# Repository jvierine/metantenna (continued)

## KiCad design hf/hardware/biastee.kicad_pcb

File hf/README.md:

# Broadband HF active dipole — development prototype

Balanced high-impedance X/Y inputs use paired MMBFJ310 JFET followers and BC850C output buffers. The nominal passband is 0.1–30 MHz. Only the X coax carries 12 V DC; both polarizations have common-mode filtering at the indoor bias board.

**This prototype is not RF-qualified or ready to order.** Native CAD checks pass, but the complete antenna/noise target, stability, blocker linearity and installed common-mode suppression still require validation. High input resistance alone does not establish sensitivity.

## Antenna head

## Indoor bias tee

The bias tee sits beside the receiver; the amplifier sits at the antenna. Only X supplies DC, while both coax paths include common-mode filtering.

- [KiCad schematic and PCB sources](hardware/)
- [Circuit overview](frontend.pdf)
- [Simulation and noise screening](../simulation/hf/)
- [Input-stage screening](docs/hf_frontend_screening.png)
- [Common-mode choke screening](docs/hf_choke_screening.png)
- [Shared enclosure sources](../mechanical/)

Shared generators remain in [`../hardware/`](../hardware/): `build_hf.py`, `finalize_hf.py` and `check_hf_native.py`. Use base conda Python. The mechanical interfaces reuse the VHF connector positions; confirm the exact assembled parts against the case before manufacture.

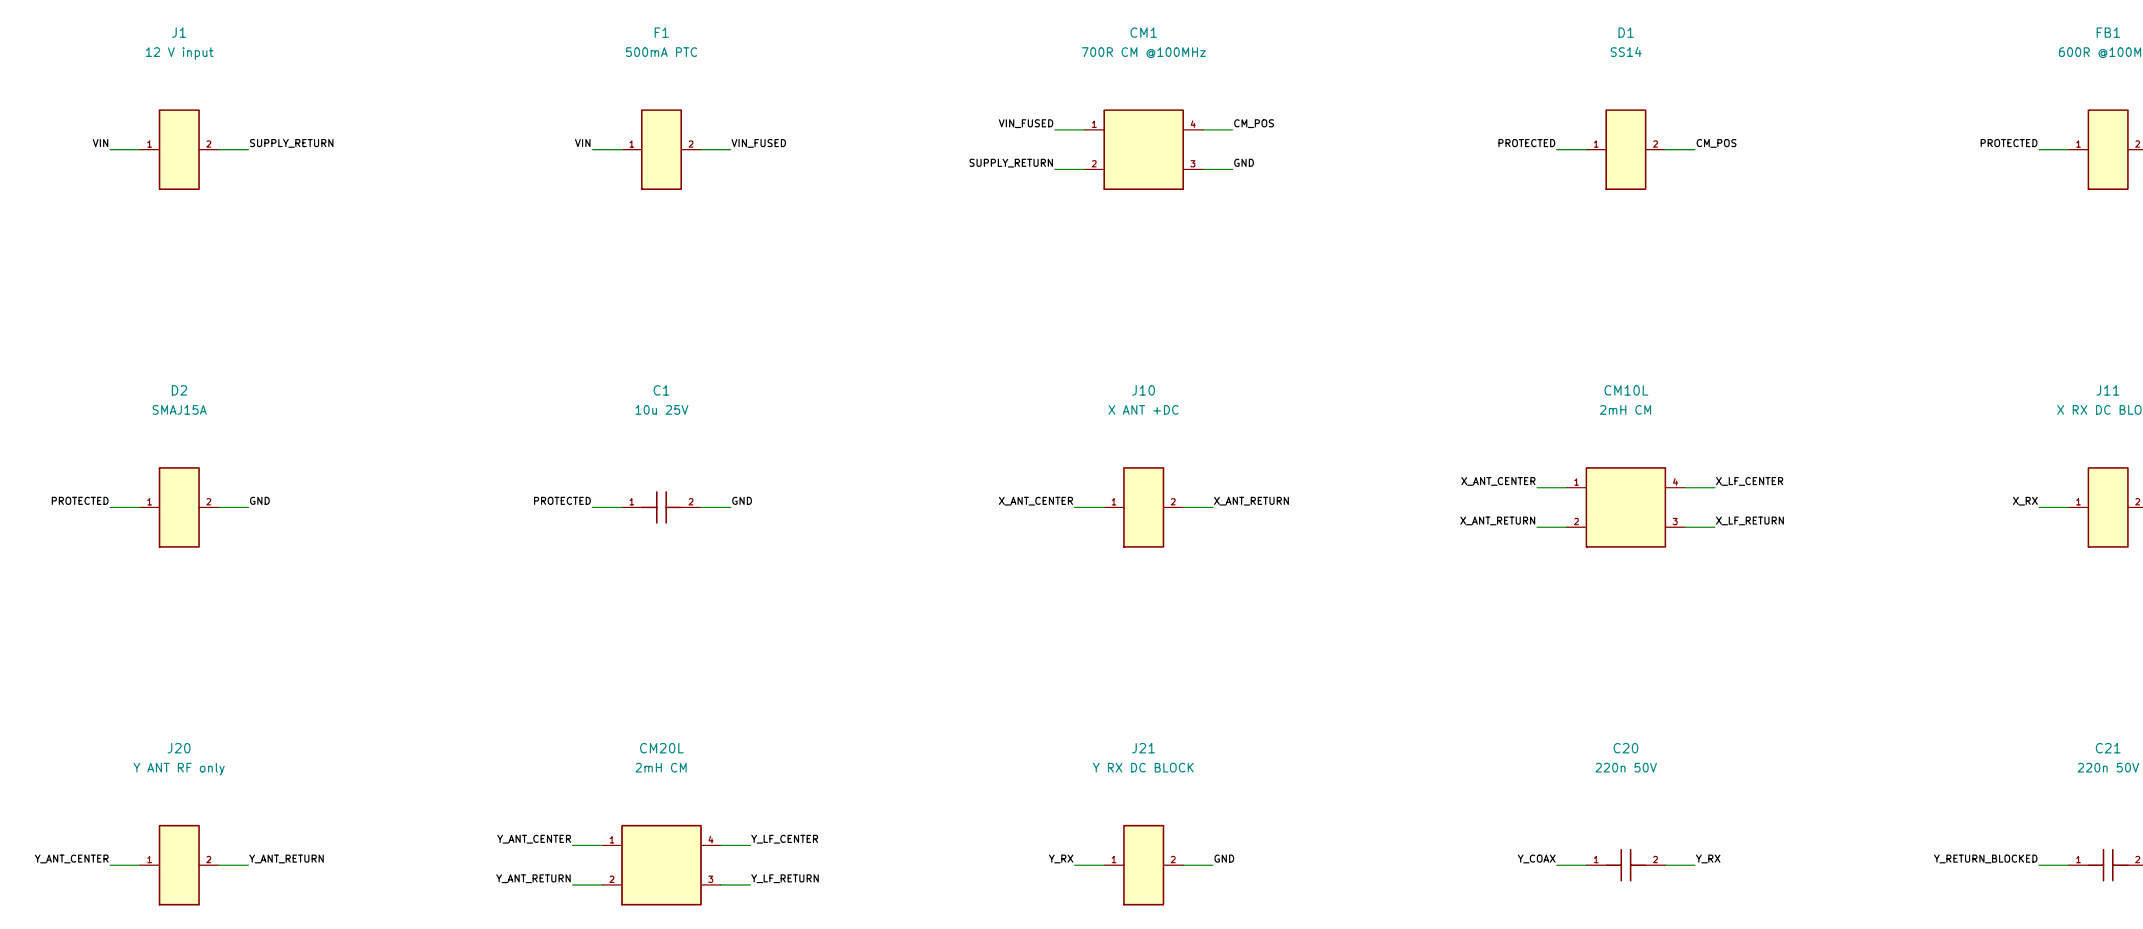
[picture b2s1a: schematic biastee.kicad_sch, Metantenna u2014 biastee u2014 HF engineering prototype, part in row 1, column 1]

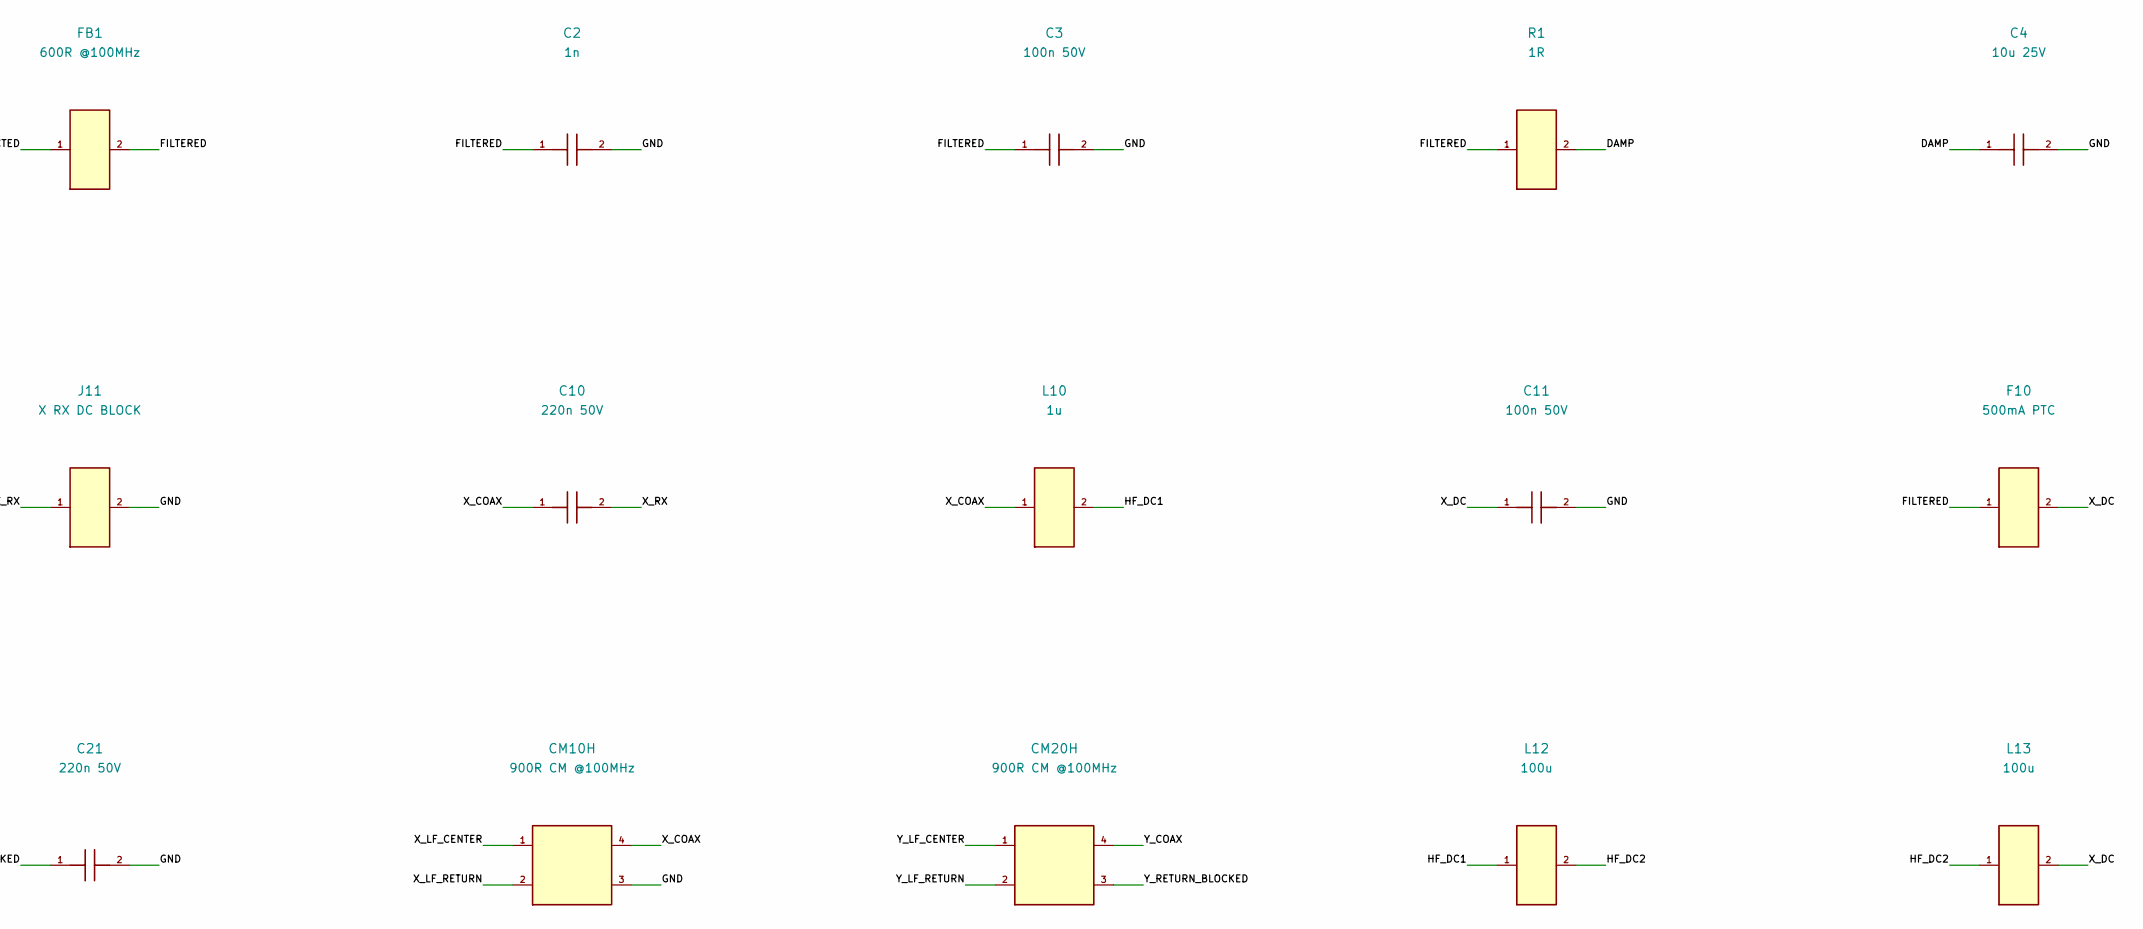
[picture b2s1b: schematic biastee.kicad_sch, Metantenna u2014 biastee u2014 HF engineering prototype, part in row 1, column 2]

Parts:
C1, C4: 10u 25V; 1206; MPN GRM31CR61E106KA12L
C2: 1n; 0805; MPN C0805C102J5GACTU
C3, C11: 100n 50V; 0805; MPN GRM21BR71H104KA01L
C10, C20, C21: 220n 50V; 0805; MPN GRM21BR71H224KA01L
CM1: 700R CM @100MHz; ACM7060; MPN ACM7060-701-2PL-TL01
CM10H, CM20H: 900R CM @100MHz; ACM4520; MPN ACM4520-901-2P-T000
CM10L, CM20L: 2mH CM; SRF0905; MPN SRF0905-202Y
D1: SS14; SMA_DIODE; MPN SS14
D2: SMAJ15A; SMA_DIODE; MPN SMAJ15A
F1, F10: 500mA PTC; 1206; MPN 1206L050/24YR
FB1: 600R @100MHz; 0805; MPN BLM21PG601SN1D
J1: 12 V input; TERM2; MPN 1729128
J10: X ANT +DC; SMA_RA; MPN SMA-KWE-323C-H13X23-LW
J11: X RX DC BLOCK; SMA_RA; MPN SMA-KWE-323C-H13X23-LW
J20: Y ANT RF only; SMA_RA; MPN SMA-KWE-323C-H13X23-LW
J21: Y RX DC BLOCK; SMA_RA; MPN SMA-KWE-323C-H13X23-LW
L10: 1u; 1008; MPN 1008CS-102XJRC
L12, L13: 100u; SRN6045; MPN SRN6045-101M
R1: 1R; 0805; MPN RC0805FR-071RL

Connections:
/CM_POS: CM1.4, D1.2
/DAMP: C4.1, R1.2
/FILTERED: C2.1, C3.1, F10.1, FB1.2, R1.1
/GND: C1.2, C2.2, C3.2, C4.2, C11.2, C21.2, CM1.3, CM10H.3, D2.2, J11.2, J21.2
/HF_DC1: L10.2, L12.1
/HF_DC2: L12.2, L13.1
/PROTECTED: C1.1, D1.1, D2.1, FB1.1
/SUPPLY_RETURN: CM1.2, J1.2
/VIN: F1.1, J1.1
/VIN_FUSED: CM1.1, F1.2
/X_ANT_CENTER: CM10L.1, J10.1
/X_ANT_RETURN: CM10L.2, J10.2
/X_COAX: C10.1, CM10H.4, L10.1
/X_DC: C11.1, F10.2, L13.2
/X_LF_CENTER: CM10H.1, CM10L.4
/X_LF_RETURN: CM10H.2, CM10L.3
/X_RX: C10.2, J11.1
/Y_ANT_CENTER: CM20L.1, J20.1
/Y_ANT_RETURN: CM20L.2, J20.2
/Y_COAX: C20.1, CM20H.4
/Y_LF_CENTER: CM20H.1, CM20L.4
/Y_LF_RETURN: CM20H.2, CM20L.3
/Y_RETURN_BLOCKED: C21.1, CM20H.3
/Y_RX: C20.2, J21.1

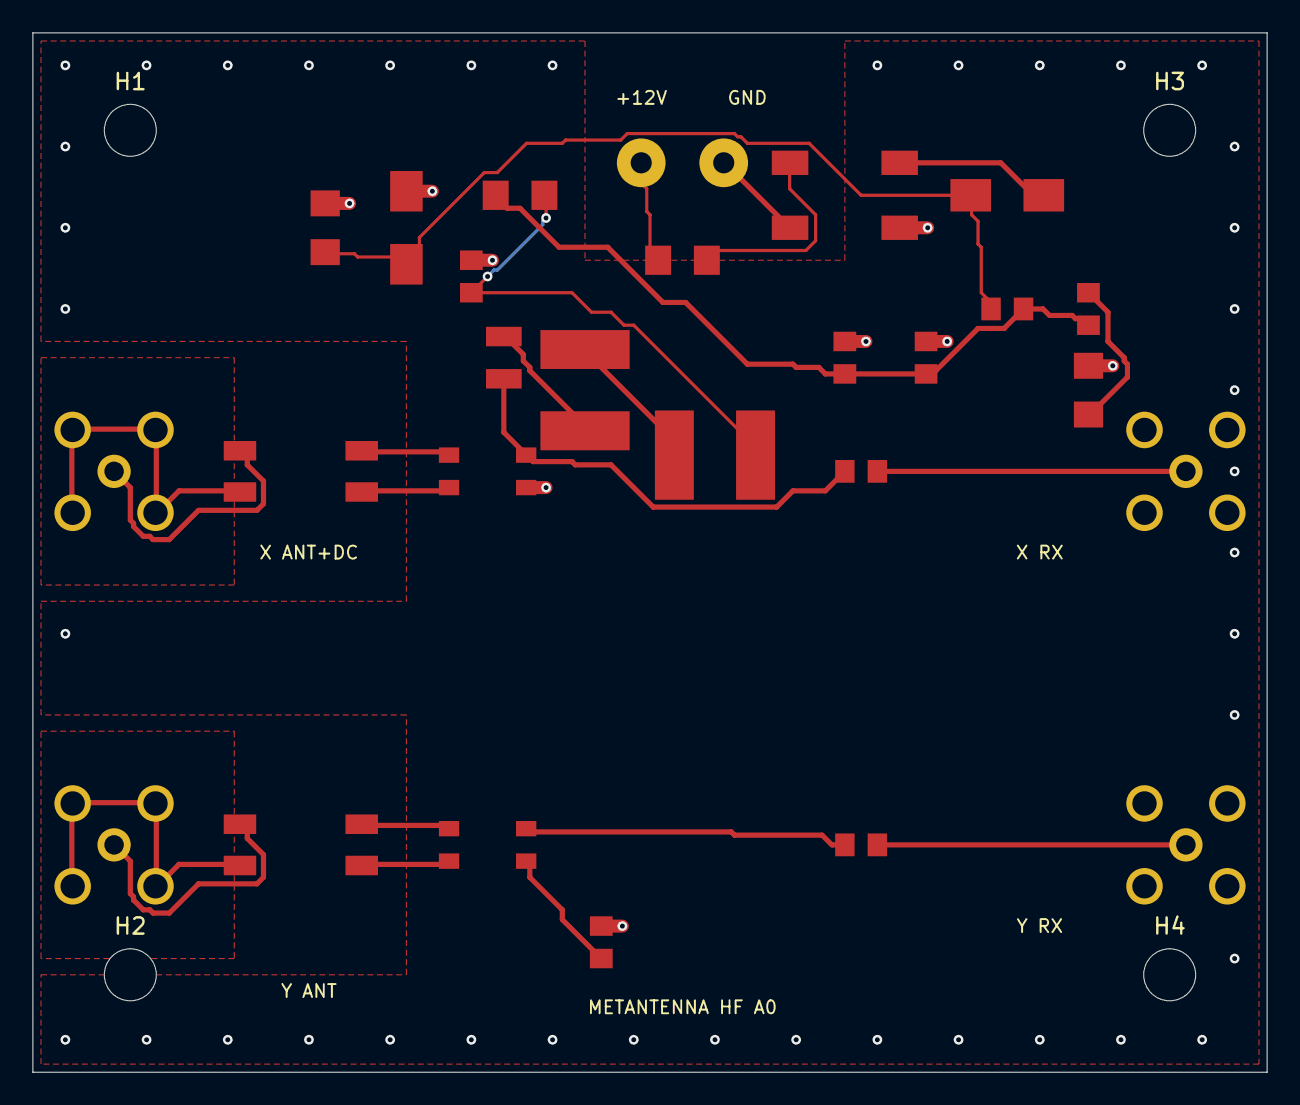
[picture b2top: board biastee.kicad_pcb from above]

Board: 4 copper layers, 76.0 x 64.0 mm, 31 parts (0 on the bottom side), 24 nets.

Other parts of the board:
H1, H2, H3, H4: MountingHole

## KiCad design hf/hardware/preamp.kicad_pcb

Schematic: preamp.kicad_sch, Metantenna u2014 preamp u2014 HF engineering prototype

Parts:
C108, C109, C130, C140, C208, C209, C230, C240: 220n 50V; 0805; MPN GRM21BR71H224KA01L
C110, C112, C210, C212: 10u 25V; 1206; MPN GRM31CR61E106KA12L
C111, C114, C211, C214: 100n 50V; 0805; MPN GRM21BR71H104KA01L
C113, C213: 10n 50V; 0805; MPN GRM21BR71H103KA01L
C131, C141, C231, C241: 100n; 0805; MPN GRM21BR71H104KA01L
C160, C161, C260, C261: 33n; 0805; MPN C0805C333J5GACTU
C162, C164, C262, C264: 130p; 0805; MPN C0805C131J5GACTU
C163, C263: 220p; 0805; MPN C0805C221J5GACTU
D103: SS14; SMA_DIODE; MPN SS14
D104: SMAJ15A; SMA_DIODE; MPN SMAJ15A
J101: X dipole; ANT_M3
J102: X RF +12V; SMA; MPN SMA-KE-347A-H13.5-P
J201: Y dipole; ANT_M3
J202: Y RF, DC blocked; SMA; MPN SMA-KE-347A-H13.5-P
L104: 1u; 1008; MPN 1008CS-102XJRC
L105, L106, L107, L205: 100u; SRN6045; MPN SRN6045-101M
L160, L260: 39u; 1008; MPN 1008CS-393XJLC
L161, L164, L261, L264: 120n; 0805; MPN 0805HP-121XGRC
L162, L163, L262, L263: 470n; 0805; MPN 0805HP-471XGRC
Q130, Q140, Q230, Q240: MMBFJ310LT1G; SOT23; MPN MMBFJ310LT1G
Q131, Q141, Q231, Q241: BC850C,235; SOT23; MPN BC850C,235
R103, R105, R203, R205: 294; 0805; MPN RC0805FR-07294RL
R104, R204: 18; 0805; MPN RC0805FR-0718RL
R106, R206: 40.2k; 0805; MPN RC0805FR-0740K2L
R107, R207: 10k; 0805; MPN RC0805FR-0710KL
R108, R208: 15 1W; 2512; MPN CRCW251215R0FKEG
R130, R140, R230, R240: 1M; 0805; MPN RC0805FR-071ML
R131, R141, R231, R241: 180; 0805; MPN RC0805FR-07180RL
R132, R142, R232, R242: 220; 0805; MPN RC0805FR-07220RL
R133, R143, R233, R243: 2.2; 0805; MPN RC0805FR-072R2L
R134, R144, R234, R244: 10; 0805; MPN RC0805FR-0710RL
R160, R260: 39; 0805; MPN RC0805FR-0739RL
T101, T201: ADT1-6T+; CD542; MPN ADT1-6T+
U101, U201: GALI-74+; SOT89; MPN GALI-74+
U102, U202: TPS7A4901DGNR; MSOP8EP; MPN TPS7A4901DGNR

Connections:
/GND: C110.2, C111.2, C112.2, C113.2, C114.2, C131.2, C141.2, C162.2, C163.2, C164.2, C210.2, C211.2, C212.2, C213.2, C214.2, C231.2, C241.2, C262.2, C263.2, C264.2, D104.2, J102.2, J202.2, L160.2, L260.2, R103.2, R105.2, R107.2, R130.2, R131.2, R132.2, R140.2, R141.2, R142.2, R203.2, R205.2, R207.2, R230.2, R231.2, R232.2, R240.2, R241.2, R242.2, T101.6, T201.6, U101.2 (GND), U102.4 (GND), U102.9 (EP), U201.2 (GND), U202.4 (GND), U202.9 (EP)
/HF_PWR1: L104.2, L106.1
/HF_PWR2: L106.2, L107.1
/V12: C110.1, C111.1, C210.1, C211.1, D103.1, D104.1, U102.5 (EN), U102.8 (IN), U202.5 (EN), U202.8 (IN)
/X_AC_N: C130.2, R133.1
/X_AC_P: C140.2, R143.1
/X_AMP_IN: L164.2, U101.1 (IN)
/X_AMP_OUT: C108.1, L105.2, U101.3 (OUT/DC)
/X_ANT_N: J101.1, Q130.3, R130.1
/X_ANT_P: J101.2, Q140.3, R140.1
/X_BAL_N: R133.2, T101.1
/X_BAL_P: R143.2, T101.3
/X_BIAS: L105.1, R108.2
/X_COAX: C109.2, J102.1, L104.1
/X_D_N: C131.1, Q130.1, R134.2
/X_D_P: C141.1, Q140.1, R144.2
/X_EF_N: C130.1, Q131.2, R132.1
/X_EF_P: C140.1, Q141.2, R142.1
/X_FB: R106.2, R107.1, U102.2 (FB)
/X_HP0: C160.1, R160.2
/X_HP1: C160.2, C161.1, L160.1
/X_LP0: C161.2, L161.1
/X_LP1: C162.1, L161.2, L162.1
/X_LP2: C163.1, L162.2, L163.1
/X_LP3: C164.1, L163.2, L164.1
/X_NR: C113.1, U102.6 (NR/SS)
/X_PAD_IN: C108.2, R103.1, R104.1
/X_PAD_OUT: C109.1, R104.2, R105.1
/X_RAW: D103.2, L107.2
/X_RF_IN: R160.1, T101.4
/X_SF_N: Q130.2, Q131.1, R131.1
/X_SF_P: Q140.2, Q141.1, R141.1
/X_V8: C112.1, C114.1, Q131.3, Q141.3, R106.1, R108.1, R134.1, R144.1, U102.1 (OUT)
/Y_AC_N: C230.2, R233.1
/Y_AC_P: C240.2, R243.1
/Y_AMP_IN: L264.2, U201.1 (IN)
/Y_AMP_OUT: C208.1, L205.2, U201.3 (OUT/DC)
/Y_ANT_N: J201.1, Q230.3, R230.1
/Y_ANT_P: J201.2, Q240.3, R240.1
/Y_BAL_N: R233.2, T201.1
/Y_BAL_P: R243.2, T201.3
/Y_BIAS: L205.1, R208.2
/Y_COAX: C209.2, J202.1
/Y_D_N: C231.1, Q230.1, R234.2
/Y_D_P: C241.1, Q240.1, R244.2
/Y_EF_N: C230.1, Q231.2, R232.1
/Y_EF_P: C240.1, Q241.2, R242.1
/Y_FB: R206.2, R207.1, U202.2 (FB)
/Y_HP0: C260.1, R260.2
/Y_HP1: C260.2, C261.1, L260.1
/Y_LP0: C261.2, L261.1
/Y_LP1: C262.1, L261.2, L262.1
/Y_LP2: C263.1, L262.2, L263.1
/Y_LP3: C264.1, L263.2, L264.1
/Y_NR: C213.1, U202.6 (NR/SS)
/Y_PAD_IN: C208.2, R203.1, R204.1
/Y_PAD_OUT: C209.1, R204.2, R205.1
/Y_RF_IN: R260.1, T201.4
/Y_SF_N: Q230.2, Q231.1, R231.1
/Y_SF_P: Q240.2, Q241.1, R241.1
/Y_V8: C212.1, C214.1, Q231.3, Q241.3, R206.1, R208.1, R234.1, R244.1, U202.1 (OUT)

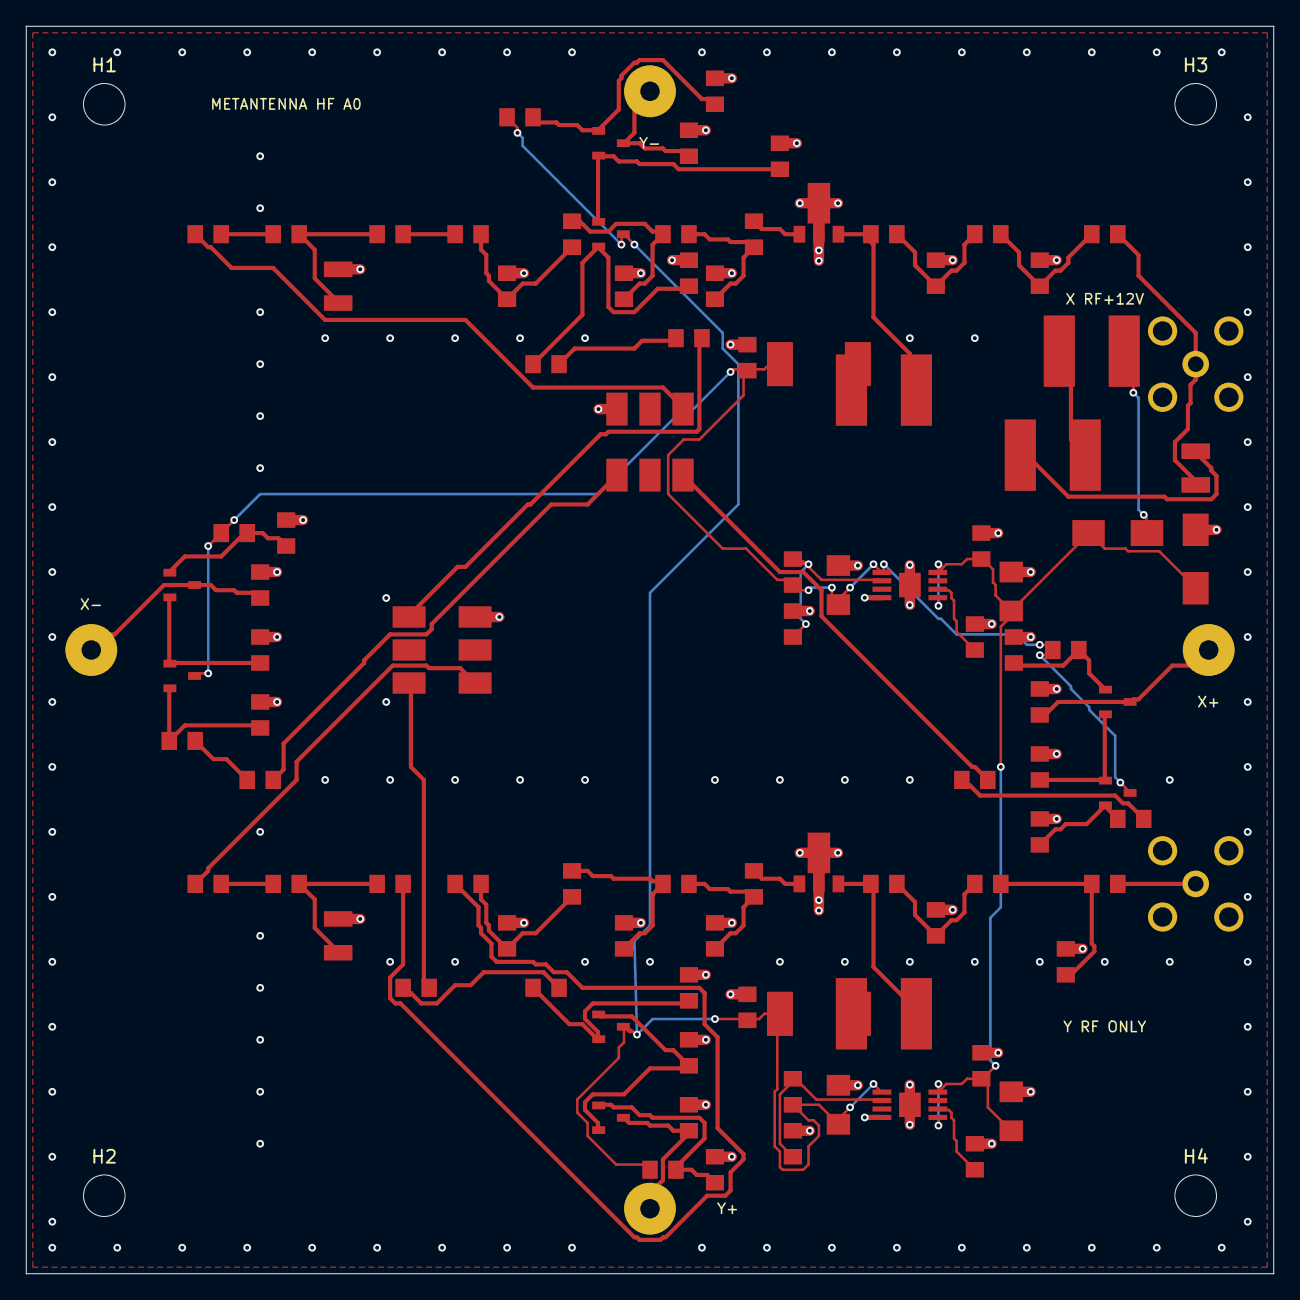
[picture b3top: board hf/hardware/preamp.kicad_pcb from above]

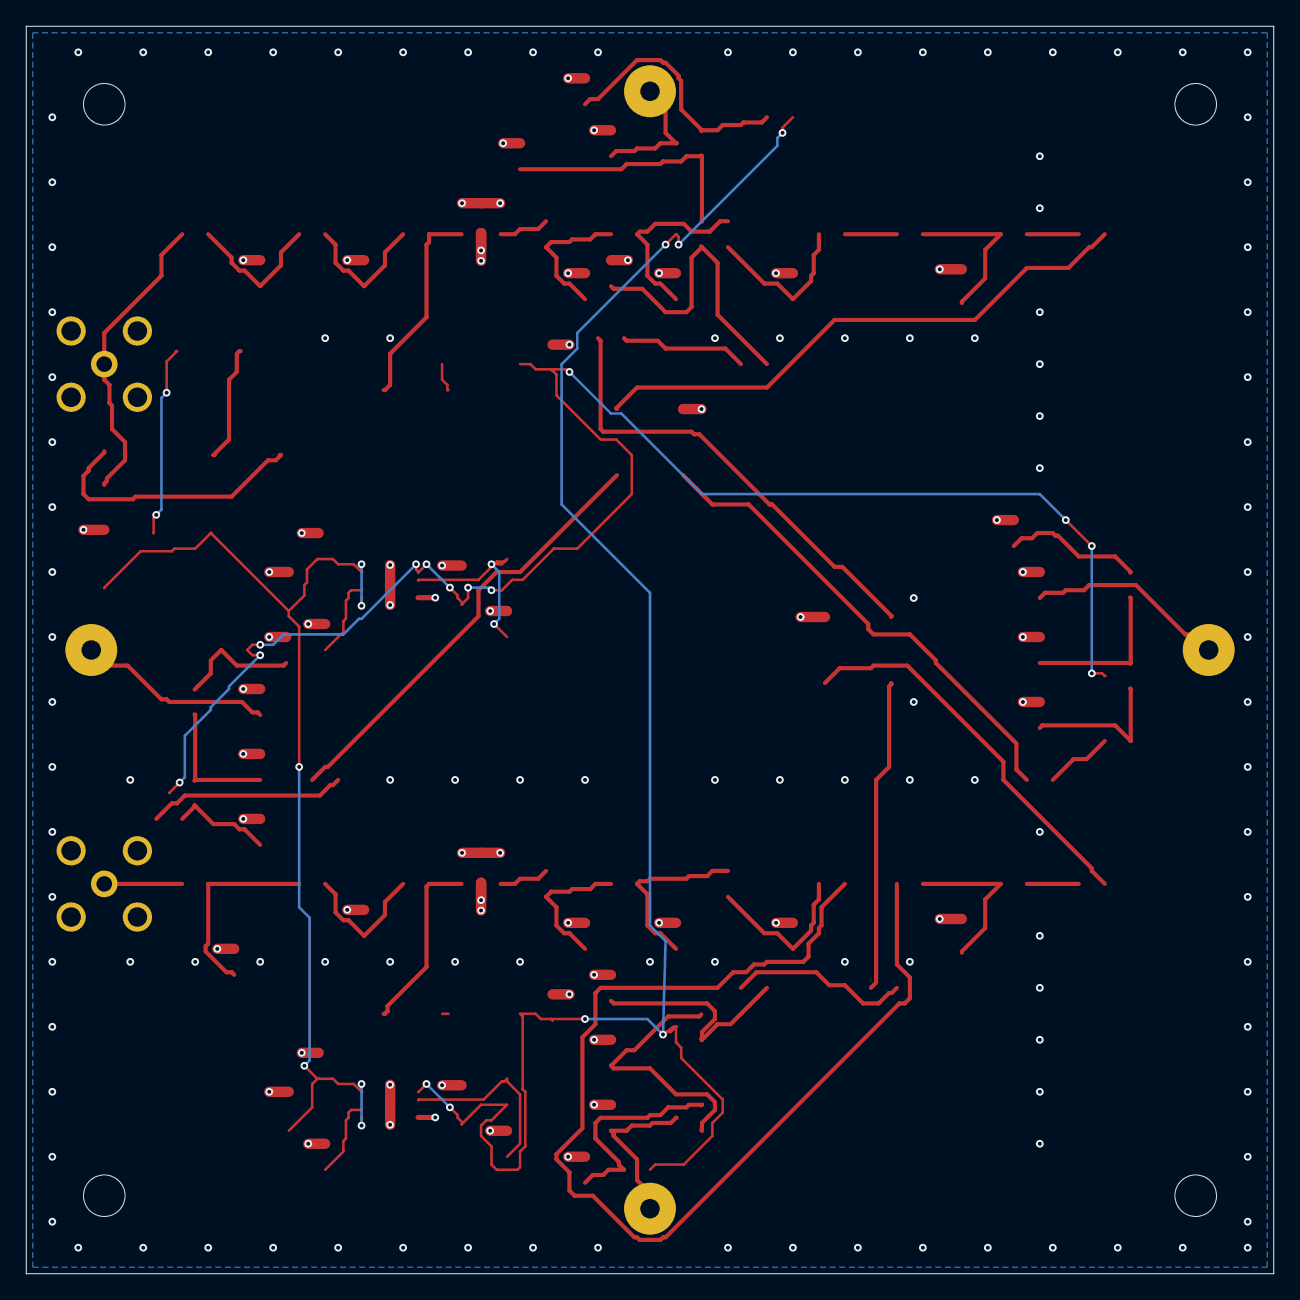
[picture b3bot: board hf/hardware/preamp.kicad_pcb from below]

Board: 4 copper layers, 96.0 x 96.0 mm, 105 parts (2 on the bottom side), 61 nets.

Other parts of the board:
H1, H2, H3, H4: MountingHole
